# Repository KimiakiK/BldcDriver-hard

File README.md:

# BLDC Driver
[Software](https://github.com/KimiakiK/BldcDriver-soft)

# Features
- ブラシレスDCモーターの回転制御

# Major Components  
- STM32F303K8
- IR2101
- Nch Power MOSFET

# Photos

## PCB
- V3.2

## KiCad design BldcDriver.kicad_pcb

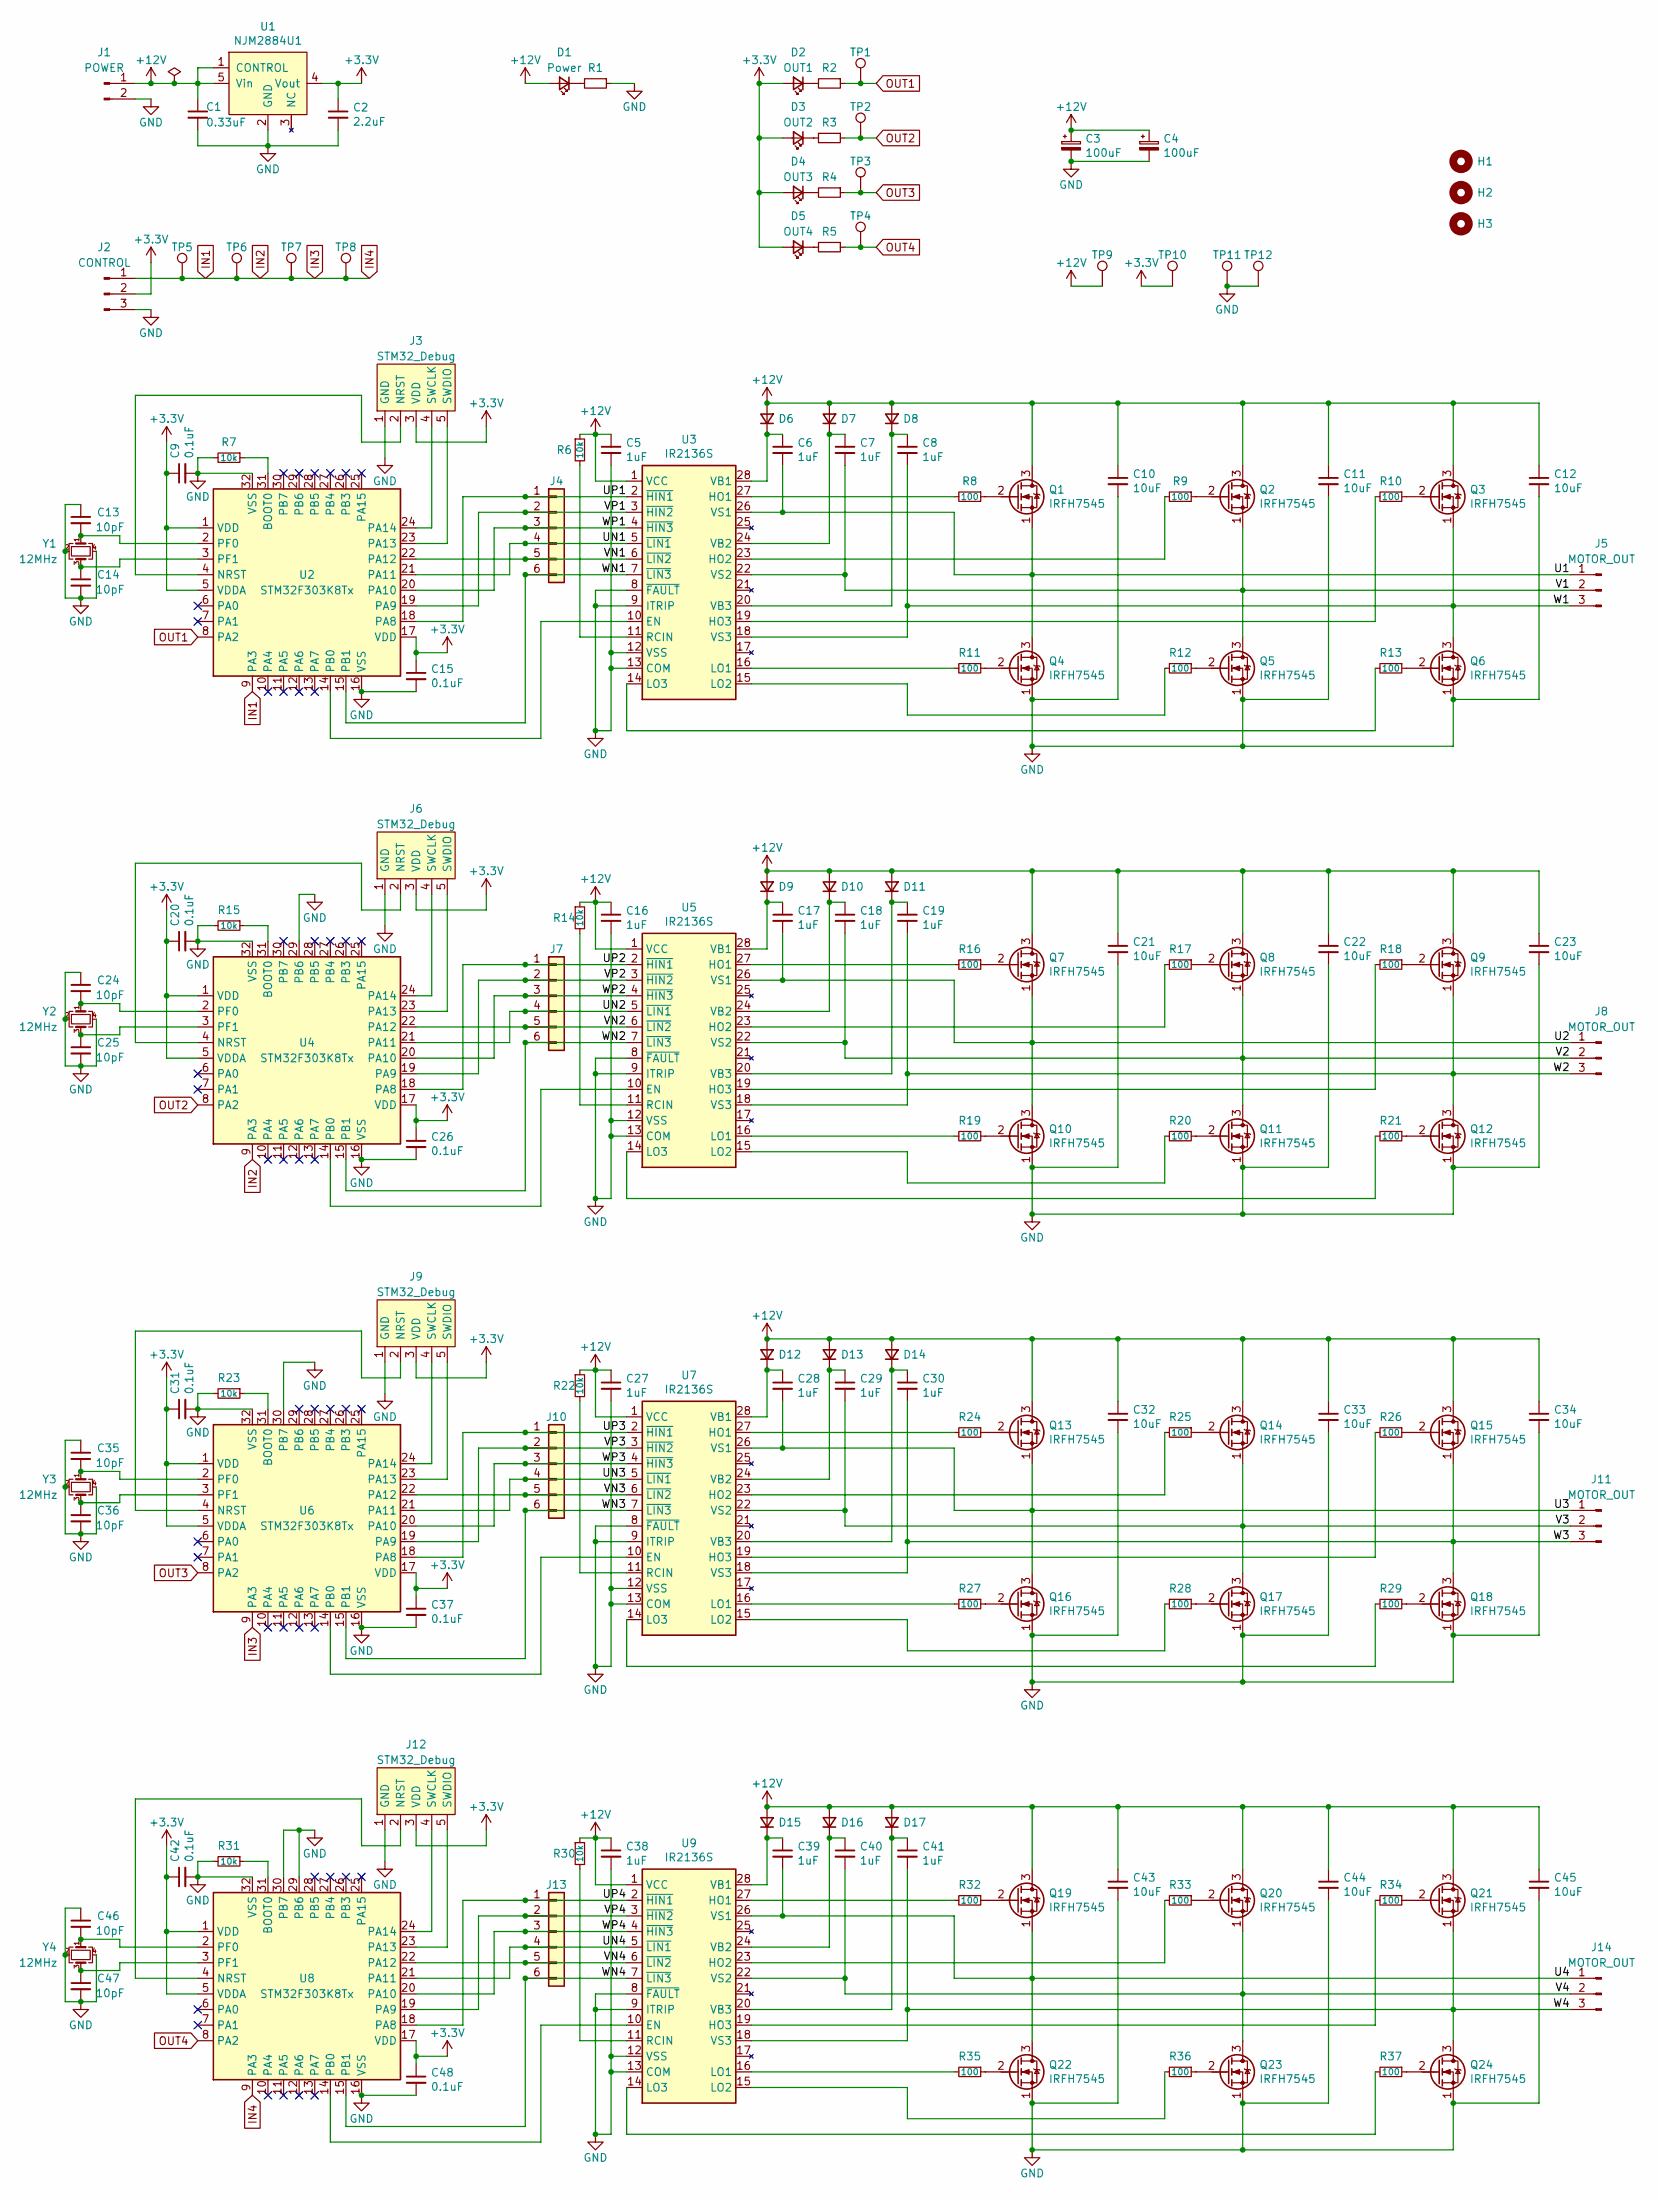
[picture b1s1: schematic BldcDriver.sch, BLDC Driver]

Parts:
C1: 0.33uF; 1608Metric
C2: 2.2uF; 1608Metric
C3, C4: 100uF; CP_Elec_6.3x7.7
C5, C6, C7, C8, C16, C17, C18, C19, C27, C28, C29, C30, C38, C39, C40, C41: 1uF; 1608Metric
C9, C15, C20, C26, C31, C37, C42, C48: 0.1uF; 1608Metric
C10, C11, C12, C21, C22, C23, C32, C33, C34, C43, C44, C45: 10uF; 1608Metric
C13, C14, C24, C25, C35, C36, C46, C47: 10pF; 1005Metric
D1: Power; 1608Metric
D2: OUT1; 1608Metric
D3: OUT2; 1608Metric
D4: OUT3; 1608Metric
D5: OUT4; 1608Metric
D6, D7, D8, D9, D10, D11, D12, D13, D14, D15, D16, D17: 1N4148W; D_SOD-123
H1: MountingHole; MountingHole_4.3mm_M4
H2, H3: MountingHole; MountingHole_2mm
J1: POWER; JST_XH_S2B-XH-A_1x02_P2.50mm_Horizontal
J2: CONTROL; JST_XH_S3B-XH-A_1x03_P2.50mm_Horizontal
J3, J6, J9, J12: STM32_Debug; STM32_Debug_5pin
J4, J7, J10, J13: Conn_01x06; Pin_1x06_P2.54mm
J5, J8, J11, J14: MOTOR_OUT; JST_XH_S3B-XH-A_1x03_P2.50mm_Horizontal
Q1, Q2, Q3, Q4, Q5, Q6, Q7, Q8, Q9, Q10, Q11, Q12, Q13, Q14, Q15, Q16, Q17, Q18, Q19, Q20, Q21, Q22, Q23, Q24: IRFH7545; VSONP-8-1EP_5x6_P1.27mm
R1, R2, R3, R4, R5: R; 1608Metric
R6, R7, R14, R15, R22, R23, R30, R31: 10k; 1608Metric
R8, R9, R10, R11, R12, R13, R16, R17, R18, R19, R20, R21, R24, R25, R26, R27, R28, R29, R32, R33, R34, R35, R36, R37: 100; 1608Metric
TP1, TP2, TP3, TP4, TP5, TP6, TP7, TP8, TP9, TP10, TP11, TP12: TestPoint; TestPoint_THTPad_D1.3mm_Drill0.9mm
U1: NJM2884U1; SOT-89-5
U2, U4, U6, U8: STM32F303K8Tx; LQFP-32_7x7mm_P0.8mm_FusionPCB
U3, U5, U7, U9: IR2136S; SOIC-28W_7.5x17.9mm_P1.27mm
Y1, Y2, Y3, Y4: 12MHz; Crystal_SMD_3225-4Pin_3.2x2.5mm_HandSoldering

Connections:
+3V3: C2.1, C9.1, C15.1, C20.1, C26.1, C31.1, C37.1, C42.1, C48.1, D2.2 (A), D3.2 (A), D4.2 (A), D5.2 (A), J2.2, J3.3 (VDD), J6.3 (VDD), J9.3 (VDD), J12.3 (VDD), TP10.1, U1.4 (Vout), U2.1 (VDD), U2.5 (VDDA), U2.17 (VDD), U4.1 (VDD), U4.5 (VDDA), U4.17 (VDD), U6.1 (VDD), U6.5 (VDDA), U6.17 (VDD), U8.1 (VDD), U8.5 (VDDA), U8.17 (VDD)
+12V: C1.1, C3.1, C4.1, C5.1, C10.1, C11.1, C12.1, C16.1, C21.1, C22.1, C23.1, C27.1, C32.1, C33.1, C34.1, C38.1, C43.1, C44.1, C45.1, D1.2 (A), D6.2 (A), D7.2 (A), D8.2 (A), D9.2 (A), D10.2 (A), D11.2 (A), D12.2 (A), D13.2 (A), D14.2 (A), D15.2 (A), D16.2 (A), D17.2 (A), J1.1, Q1.3 (D), Q2.3 (D), Q3.3 (D), Q7.3 (D), Q8.3 (D), Q9.3 (D), Q13.3 (D), Q14.3 (D), Q15.3 (D), Q19.3 (D), Q20.3 (D), Q21.3 (D), R6.1, R14.1, R22.1, R30.1, TP9.1, U1.1 (CONTROL), U1.5 (Vin), U3.1 (VCC), U5.1 (VCC), U7.1 (VCC), U9.1 (VCC)
/U1: C6.2, J5.1, Q1.1 (S), Q4.3 (D), U3.26 (VS1)
/U2: C17.2, J8.1, Q7.1 (S), Q10.3 (D), U5.26 (VS1)
/U3: C28.2, J11.1, Q13.1 (S), Q16.3 (D), U7.26 (VS1)
/U4: C39.2, J14.1, Q19.1 (S), Q22.3 (D), U9.26 (VS1)
/UN1: J4.4, U2.21 (PA11), U3.5 (~LIN1)
/UN2: J7.4, U4.21 (PA11), U5.5 (~LIN1)
/UN3: J10.4, U6.21 (PA11), U7.5 (~LIN1)
/UN4: J13.4, U8.21 (PA11), U9.5 (~LIN1)
/UP1: J4.1, U2.18 (PA8), U3.2 (~HIN1)
/UP2: J7.1, U4.18 (PA8), U5.2 (~HIN1)
/UP3: J10.1, U6.18 (PA8), U7.2 (~HIN1)
/UP4: J13.1, U8.18 (PA8), U9.2 (~HIN1)
/V1: C7.2, J5.2, Q2.1 (S), Q5.3 (D), U3.22 (VS2)
/V2: C18.2, J8.2, Q8.1 (S), Q11.3 (D), U5.22 (VS2)
/V3: C29.2, J11.2, Q14.1 (S), Q17.3 (D), U7.22 (VS2)
/V4: C40.2, J14.2, Q20.1 (S), Q23.3 (D), U9.22 (VS2)
/VN1: J4.5, U2.22 (PA12), U3.6 (~LIN2)
/VN2: J7.5, U4.22 (PA12), U5.6 (~LIN2)
/VN3: J10.5, U6.22 (PA12), U7.6 (~LIN2)
/VN4: J13.5, U8.22 (PA12), U9.6 (~LIN2)
/VP1: J4.2, U2.19 (PA9), U3.3 (~HIN2)
/VP2: J7.2, U4.19 (PA9), U5.3 (~HIN2)
/VP3: J10.2, U6.19 (PA9), U7.3 (~HIN2)
/VP4: J13.2, U8.19 (PA9), U9.3 (~HIN2)
/W1: C8.2, J5.3, Q3.1 (S), Q6.3 (D), U3.18 (VS3)
/W2: C19.2, J8.3, Q9.1 (S), Q12.3 (D), U5.18 (VS3)
/W3: C30.2, J11.3, Q15.1 (S), Q18.3 (D), U7.18 (VS3)
/W4: C41.2, J14.3, Q21.1 (S), Q24.3 (D), U9.18 (VS3)
/WN1: J4.6, U2.15 (PB1), U3.7 (~LIN3)
/WN2: J7.6, U4.15 (PB1), U5.7 (~LIN3)
/WN3: J10.6, U6.15 (PB1), U7.7 (~LIN3)
/WN4: J13.6, U8.15 (PB1), U9.7 (~LIN3)
/WP1: J4.3, U2.20 (PA10), U3.4 (~HIN3)
/WP2: J7.3, U4.20 (PA10), U5.4 (~HIN3)
/WP3: J10.3, U6.20 (PA10), U7.4 (~HIN3)
/WP4: J13.3, U8.20 (PA10), U9.4 (~HIN3)
GND: C1.2, C2.2, C3.2, C4.2, C5.2, C9.2, C10.2, C11.2, C12.2, C13.1, C14.2, C15.2, C16.2, C20.2, C21.2, C22.2, C23.2, C24.1, C25.2, C26.2, C27.2, C31.2, C32.2, C33.2, C34.2, C35.1, C36.2, C37.2, C38.2, C42.2, C43.2, C44.2, C45.2, C46.1, C47.2, C48.2, J1.2, J2.3, J3.1 (GND), J6.1 (GND), J9.1 (GND), J12.1 (GND), Q4.1 (S), Q5.1 (S), Q6.1 (S), Q10.1 (S), Q11.1 (S), Q12.1 (S), Q16.1 (S), Q17.1 (S), Q18.1 (S), Q22.1 (S), Q23.1 (S), Q24.1 (S), R1.1, R7.2, R15.2, R23.2, R31.2, TP11.1, TP12.1, U1.2 (GND), U2.16 (VSS), U2.32 (VSS), U3.8 (~FAULT), U3.9 (ITRIP), U3.12 (VSS), U3.13 (COM), U4.16 (VSS), U4.29 (PB6), U4.32 (VSS), U5.8 (~FAULT), U5.9 (ITRIP), U5.12 (VSS), U5.13 (COM), U6.16 (VSS), U6.30 (PB7), U6.32 (VSS), U7.8 (~FAULT), U7.9 (ITRIP), U7.12 (VSS), U7.13 (COM), U8.16 (VSS), U8.29 (PB6), U8.30 (PB7), U8.32 (VSS), U9.8 (~FAULT), U9.9 (ITRIP), U9.12 (VSS), U9.13 (COM), Y1.2, Y1.4, Y2.2, Y2.4, Y3.2, Y3.4, Y4.2, Y4.4
IN1: J2.1, TP5.1, TP6.1, TP7.1, TP8.1, U2.9 (PA3), U4.9 (PA3), U6.9 (PA3), U8.9 (PA3)
unnamed: C6.1, D6.1 (K), U3.28 (VB1)
unnamed: C7.1, D7.1 (K), U3.24 (VB2)
unnamed: C8.1, D8.1 (K), U3.20 (VB3)
unnamed: C13.2, U2.2 (PF0), Y1.1
unnamed: C14.1, U2.3 (PF1), Y1.3
unnamed: C17.1, D9.1 (K), U5.28 (VB1)
unnamed: C18.1, D10.1 (K), U5.24 (VB2)
unnamed: C19.1, D11.1 (K), U5.20 (VB3)
unnamed: C24.2, U4.2 (PF0), Y2.1
unnamed: C25.1, U4.3 (PF1), Y2.3
unnamed: C28.1, D12.1 (K), U7.28 (VB1)
unnamed: C29.1, D13.1 (K), U7.24 (VB2)
unnamed: C30.1, D14.1 (K), U7.20 (VB3)
unnamed: C35.2, U6.2 (PF0), Y3.1
unnamed: C36.1, U6.3 (PF1), Y3.3
unnamed: C39.1, D15.1 (K), U9.28 (VB1)
unnamed: C40.1, D16.1 (K), U9.24 (VB2)
unnamed: C41.1, D17.1 (K), U9.20 (VB3)
unnamed: C46.2, U8.2 (PF0), Y4.1
unnamed: C47.1, U8.3 (PF1), Y4.3
unnamed: D1.1 (K), R1.2
unnamed: D2.1 (K), R2.2
unnamed: D3.1 (K), R3.2
unnamed: D4.1 (K), R4.2
unnamed: D5.1 (K), R5.2
unnamed: J3.2 (NRST), U2.4 (NRST)
unnamed: J3.4 (SWCLK), U2.24 (PA14)
unnamed: J3.5 (SWDIO), U2.23 (PA13)
unnamed: J6.2 (NRST), U4.4 (NRST)
unnamed: J6.4 (SWCLK), U4.24 (PA14)
unnamed: J6.5 (SWDIO), U4.23 (PA13)
unnamed: J9.2 (NRST), U6.4 (NRST)
unnamed: J9.4 (SWCLK), U6.24 (PA14)
unnamed: J9.5 (SWDIO), U6.23 (PA13)
unnamed: J12.2 (NRST), U8.4 (NRST)
unnamed: J12.4 (SWCLK), U8.24 (PA14)
unnamed: J12.5 (SWDIO), U8.23 (PA13)
unnamed: Q1.2 (G), R8.1
unnamed: Q2.2 (G), R9.1
unnamed: Q3.2 (G), R10.1
unnamed: Q4.2 (G), R11.1
unnamed: Q5.2 (G), R12.1
unnamed: Q6.2 (G), R13.1
unnamed: Q7.2 (G), R16.1
unnamed: Q8.2 (G), R17.1
unnamed: Q9.2 (G), R18.1
unnamed: Q10.2 (G), R19.1
unnamed: Q11.2 (G), R20.1
unnamed: Q12.2 (G), R21.1
unnamed: Q13.2 (G), R24.1
unnamed: Q14.2 (G), R25.1
unnamed: Q15.2 (G), R26.1
unnamed: Q16.2 (G), R27.1
unnamed: Q17.2 (G), R28.1
unnamed: Q18.2 (G), R29.1
unnamed: Q19.2 (G), R32.1
unnamed: Q20.2 (G), R33.1
unnamed: Q21.2 (G), R34.1
unnamed: Q22.2 (G), R35.1
unnamed: Q23.2 (G), R36.1
unnamed: Q24.2 (G), R37.1
unnamed: R6.2, U3.11 (RCIN)
unnamed: R7.1, U2.31 (BOOT0)
unnamed: R8.2, U3.27 (HO1)
unnamed: R9.2, U3.23 (HO2)
unnamed: R10.2, U3.19 (HO3)
unnamed: R11.2, U3.16 (LO1)
unnamed: R12.2, U3.15 (LO2)
unnamed: R13.2, U3.14 (LO3)
unnamed: R14.2, U5.11 (RCIN)
unnamed: R15.1, U4.31 (BOOT0)
unnamed: R16.2, U5.27 (HO1)
unnamed: R17.2, U5.23 (HO2)
unnamed: R18.2, U5.19 (HO3)
unnamed: R19.2, U5.16 (LO1)
unnamed: R20.2, U5.15 (LO2)
unnamed: R21.2, U5.14 (LO3)
unnamed: R22.2, U7.11 (RCIN)
unnamed: R23.1, U6.31 (BOOT0)
unnamed: R24.2, U7.27 (HO1)
unnamed: R25.2, U7.23 (HO2)
unnamed: R26.2, U7.19 (HO3)
unnamed: R27.2, U7.16 (LO1)
unnamed: R28.2, U7.15 (LO2)
unnamed: R29.2, U7.14 (LO3)
unnamed: R30.2, U9.11 (RCIN)
unnamed: R31.1, U8.31 (BOOT0)
unnamed: R32.2, U9.27 (HO1)
unnamed: R33.2, U9.23 (HO2)
unnamed: R34.2, U9.19 (HO3)
unnamed: R35.2, U9.16 (LO1)
unnamed: R36.2, U9.15 (LO2)
unnamed: R37.2, U9.14 (LO3)
unnamed: U2.14 (PB0), U3.10 (EN)
unnamed: U4.14 (PB0), U5.10 (EN)
unnamed: U6.14 (PB0), U7.10 (EN)
unnamed: U8.14 (PB0), U9.10 (EN)
OUT1: R2.1, TP1.1, U2.8 (PA2)
OUT2: R3.1, TP2.1, U4.8 (PA2)
OUT3: R4.1, TP3.1, U6.8 (PA2)
OUT4: R5.1, TP4.1, U8.8 (PA2)

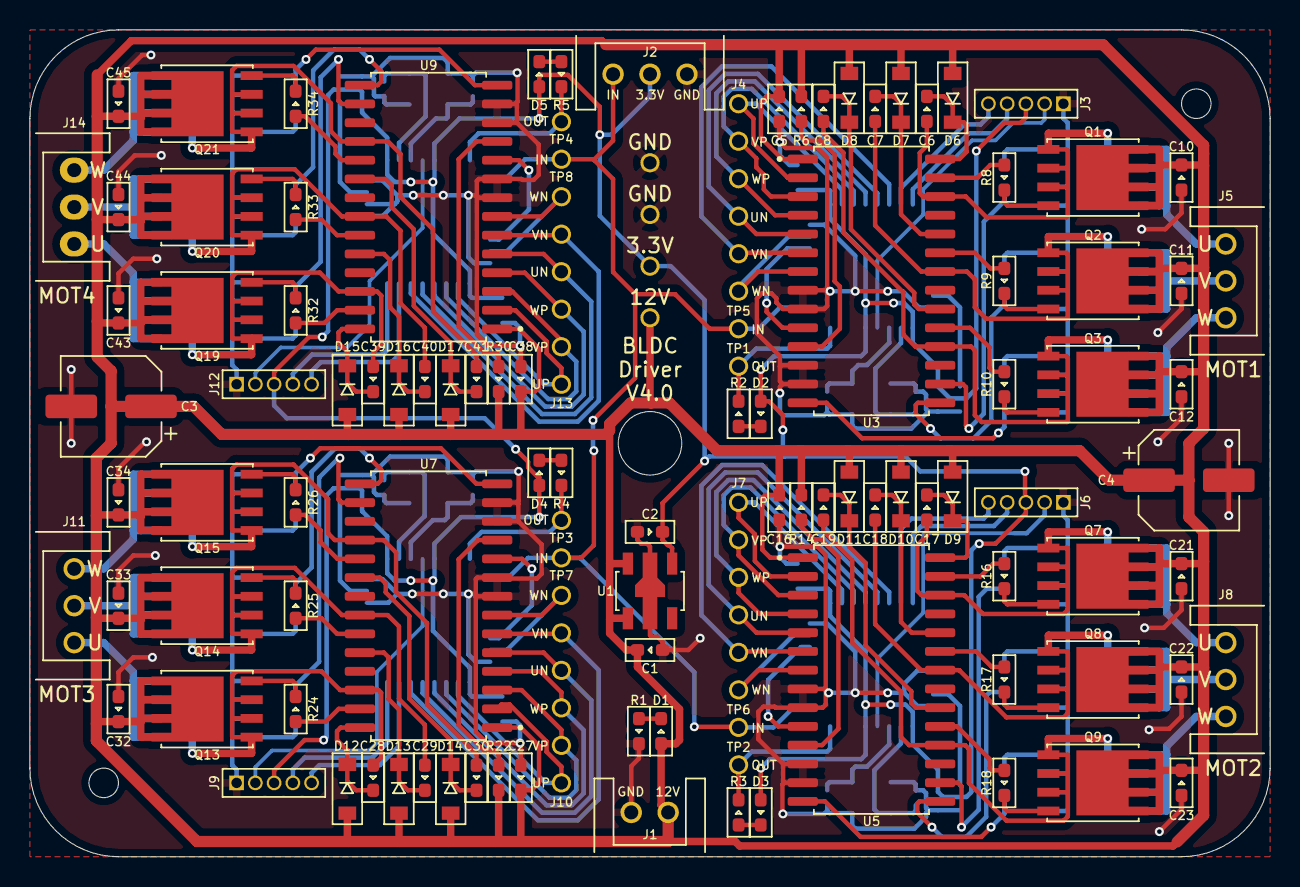
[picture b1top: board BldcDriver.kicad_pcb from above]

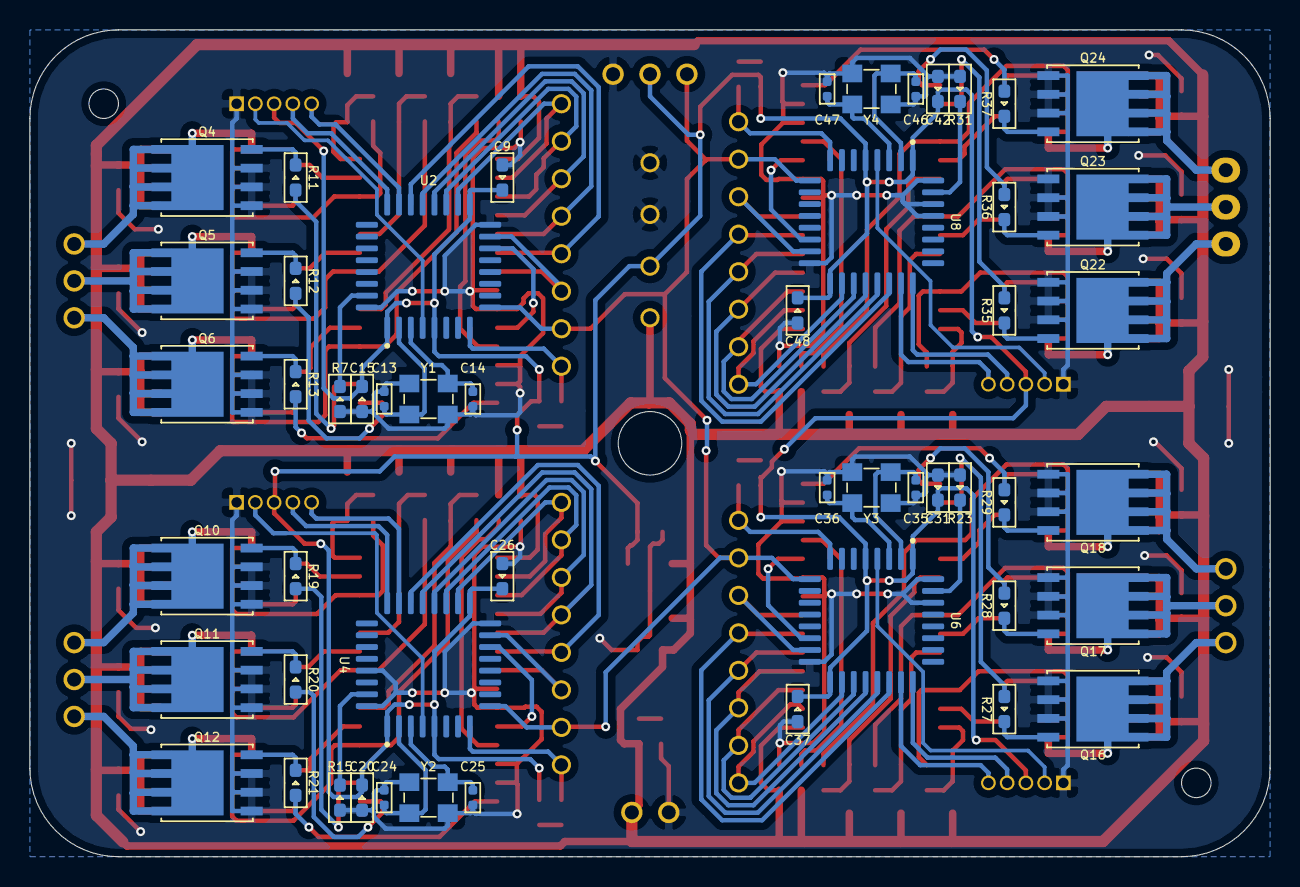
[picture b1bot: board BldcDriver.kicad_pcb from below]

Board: 2 copper layers, 84.0 x 56.0 mm, 168 parts (52 on the bottom side), 141 nets.

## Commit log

2021-04-27 基板V3.2
2021-04-29 Add images
2021-08-13 基板 V4.0
